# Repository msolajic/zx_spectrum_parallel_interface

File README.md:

# zx_spectrum_parallel_interface
Hardware design for a 3-port Parallel Interface for the Sinclair ZX Spectrum computer, with accompanying software examples.

This project is free to use and you can use any PCB manufacturer by downloading the Gerber files, but if you would like to support my work and help with further hardware development you can order these PCBs on PCBWay trough this link:

You will get cheap and professionally made PCBs, I will get credits that will help with this and [other projects](https://www.pcbway.com/project/member/?bmbno=1DE407A1-1650-47). Also, if you have to register to that site, [you can use this link](https://pcbway.com/g/YFnBAc) to get bonus initial credit.

Hardware Description
--------------------
The interface adds three 8-bit general-purpose buffered input-output ports to the ZX Spectrum, enabling you to create additional boards which use these ports as A/D or D/A convertres, motor drivers, relays, or, for example, use some Arduino modules. It also has an on-board Joystick port (on standard Port 31 for Kempston interface compatibility) and a Parallel (Centronics compatible) printer port.

It is built with Intel 8255 PPI chip, which is programmable - each 8-bit port can be set to either input or output (and there are special modes which split the 3rd port in 4 inputs and 4 outputs or enable handshaking). Refer to the [Intel 8255 documentation](./images/8255_intel.pdf "Intel 8255 documentation") for details.

The Interface is based on similar interfaces, especially [UR-4](https://cygnus.speccy.cz/popis_mhb8255.php "UR-4") and [UPI](https://cygnus.speccy.cz/popis_upi-jiiira-8255.php "UPI")

A 74LS688 forms an address decoder, to fully decode the addresses in the Input/Output Address space, so no "ghost" addresses can trigger the interface. 74LS04 is used to invert the RESET signal (as the 8255 requires a positive logic signal there) and to invert the STROBE signal for the printer. 74LS540 is used as an additional 3-state buffer for the Joystick port, which can be disabled via a switch (if you don't need the joystick port and plan to use the port A for other purposes)

Port Pinouts
------------

#### Joystick port

| DB-9 Pin | Port A | Joystick | Amiga Mouse       |
|:--------:|:------:|:--------:|:-----------------:|
| 1        | 3      | Up       | Y2 (YB)           |
| 2        | 2      | Down     | X1 (XA)           |
| 3        | 1      | Left     | Y1 (YA)           |
| 4        | 0      | Right    | X2 (XB)           |
| 5        | 6      |          | Button 3 (Middle) |
| 6        | 4      | Fire 1   | Button 1 (Left)   |
| 7        |        | +5V      | +5V               |
| 8        |        | GND      | GND               |
| 9        | 5      | Fire 2   | Button 2 (Right)  | 

When the joystick port is enabled, bit 7 of Port A is always 0.

#### Printer port

| DB-25 Pin | 8255 port   | Function   |
|:---------:|:-----------:|:----------:|
| 1         | C3 inverted | /STROBE    |
| 2         | B0          | Data bit 0 |
| 3         | B1          | Data bit 1 |
| 4         | B2          | Data bit 2 |
| 5         | B3          | Data bit 3 |
| 6         | B4          | Data bit 4 |
| 7         | B5          | Data bit 5 |
| 8         | B6          | Data bit 6 |
| 9         | B7          | Data bit 7 |
| 11        | C7          | BUSY       |
| 17        | Jumper JP1  | /SELECT    |
| 18-25     | GND         | GND        |

Some printers require pin 17 (/SELECT) pulled low. In case your printer doesn't work, short the jumper JP1.

#### 40-pin connector

| Pin | Function | | Function | Pin |
|:---:|:--------:|-|:--------:|:---:|
| 1   | A0       | | A1       | 2   |
| 3   | A2       | | A3       | 4   |
| 5   | A4       | | A5       | 6   |
| 7   | A6       | | A7       | 8   |
| 9   | GND      | | GND      | 10  |
| 11  | GND      | | GND      | 12  |
| 13  | C0       | | C1       | 14  |
| 15  | C2       | | C3       | 16  |
| 17  | C4       | | C5       | 18  |
| 19  | C6       | | C7       | 20  |
| 21  | GND      | | GND      | 22  |
| 23  | GND      | | GND      | 24  |
| 25  | B0       | | B1       | 26  |
| 27  | B2       | | B3       | 28  |
| 29  | B4       | | B5       | 30  |
| 31  | B6       | | B7       | 32  |
| 33  | NC       | | NC       | 34  |
| 35  | +9V      | | +9V      | 36  |
| 37  | NC       | | NC       | 38  |
| 39  | +5V      | | +5V      | 40  |

The connector is wired directly to the 8255 ports. +5v and +9v are from the ZX Spectrum regulator and power supply respectively. As the +5v regulator in an 48k ZX Spectrum is already at its limits, this power supply can be used only for simple logic, not for driving motors etc. For +9v output, I recommend using maximum 200mA.

Usage
-----

The interface uses the following addresses:

| Port         | Binary   | Decimal | Hex  |
|:------------:|:--------:|:-------:|:----:|
| Port A       | 00011111 | 31      | 0x1f |
| Port B       | 00111111 | 63      | 0x3f |
| Port C       | 01011111 | 95      | 0x5f |
| Control Word | 01111111 | 127     | 0x7f |

After a RESET, all ports are set as inputs. This enables the use of the Joystick port without any initialization. Setting up the direction of the ports is simple, writing a byte to the Control Word register. In Mode 0 (the simplest mode of operation for the 8255) the configuration bytes are as follows:

| Binary   | Decimal | Functions                         |
|:--------:|:-------:|:---------------------------------:|
| 10000000 | 128     | A = out B = out CL = out CH = out |
| 10000001 | 129     | A = out B = out CL = in  CH = out |
| 10000010 | 130     | A = out B = in  CL = out CH = out |
| 10000011 | 131     | A = out B = in  CL = in  CH = out |
| 10001000 | 136     | A = out B = out CL = out CH = in  |
| 10001001 | 137     | A = out B = out CL = in  CH = in  |
| 10001010 | 138     | A = out B = in  CL = out CH = in  |
| 10001011 | 139     | A = out B = in  CL = in  CH = in  |
| 10010000 | 144     | A = in  B = out CL = out CH = out |
| 10010001 | 145     | A = in  B = out CL = in  CH = out |
| 10010010 | 146     | A = in  B = in  CL = out CH = out |
| 10010011 | 147     | A = in  B = in  CL = in  CH = out |
| 10011000 | 152     | A = in  B = out CL = out CH = in  |
| 10011001 | 153     | A = in  B = out CL = in  CH = in  |
| 10011010 | 154     | A = in  B = in  CL = out CH = in  |
| 10011011 | 155     | A = in  B = in  CL = in  CH = in  |

Mode 1 enables handshaking (with port C being used for handshaking signaling), and Mode 2 enables bidirectional data transfer on port A, port B is disabled, and port C is used for handshaking. This is covered in more depth in the 8255 datasheet.

#### Printing from BASIC

A very simple BASIC program can be used to print some text. This program will probably only work on Dot-Matrix printers. Inkjet and Laser printers usually don't understand raw text, they require graphics data to be sent either via ESC/P or PCL commands.

    10 GO SUB 9000: REM INITIALIZE
    20 LET A$="This is the text to be printed"
    30 GO SUB 9100: REM LPRINT A$
    40 GO SUB 9200: REM CR+LF
    50 GO SUB 9300: REM FF
    60 STOP
    9000 REM INITIALIZE
    9010 OUT 127,152
    9020 RETURN
    9100 REM LPRINT A$
    9110 FOR N=1 TO LEN (A$)
    9120 LET CHAR=CODE(A$(N))
    9130 OUT 63,CHAR
    9140 OUT 95,255: REM /STROBE 0
    9150 OUT 95,0: REM /STROBE 1
    9160 NEXT N
    9170 RETURN
    9200 REM CR+LF
    9210 OUT 63,13
    9220 OUT 95,255: REM /STROBE 0
    9230 OUT 95,0: REM /STROBE 1
    9240 OUT 63,10
    9250 OUT 95,255: REM /STROBE 0
    9260 OUT 95,0: REM /STROBE 1
    9270 RETURN
    9300 REM FF
    9310 OUT 63,12
    9320 OUT 95,255: REM /STROBE 0
    9330 OUT 95,0: REM /STROBE 1
    9340 RETURN
    
You can find this program in the examples folder, in .bas, .tap and .wav format. Note that the BUSY line is not taken into account in this example. It is actually not needed, as the BASIC is very slow in contrast to Assembler. 

It is better to use Assembler routines as they will allow for using LPRINT and LLIST commands from BASIC. In the examples folder, I have provided a simple printer driver which resides in the (ZX Printer) printer buffer. Alongside text printing, it provides a routine to copy the graphical content of the screen to the printer. Note that the semigraphics characters and UDGs will not be printed (or will be printed with their ASCII code equivalent).

Another assembly routine provided is one that prints the screen in 3x the size, with shading. This was printed in the magazine [Your Spectrum, Issue 4, June 1984](http://www.users.globalnet.co.uk/~jg27paw4/yr04/yr04_55.htm), by Andrew Pennell. I have adapted it to use this interface.

I have used [PASMO](https://pasmo.speccy.org/ "PASMO") to assemble the sources, but you can use any other Z80 assembler. BASIC files were converted to .tap wit [bas2tap](https://github.com/speccyorg/bas2tap "bas2tap"). Tape to WAV conversion was done with [zxtap-to-wav](https://github.com/raydac/zxtap-to-wav "zxtap-to-wav")

Revision history
----------------

- Rev.1
    - Initial release

License
-------
zx_spectrum_parallel_interface is Open Hardware licensed under the [CERN OHL P v2](https://ohwr.org/cern_ohl_p_v2.txt), released by Marko Šolajić in 2025. You may redistribute and modify this documentation under the terms of the CERN OHL P v2.

A copy of the full license is included in file [license.txt](license.txt)

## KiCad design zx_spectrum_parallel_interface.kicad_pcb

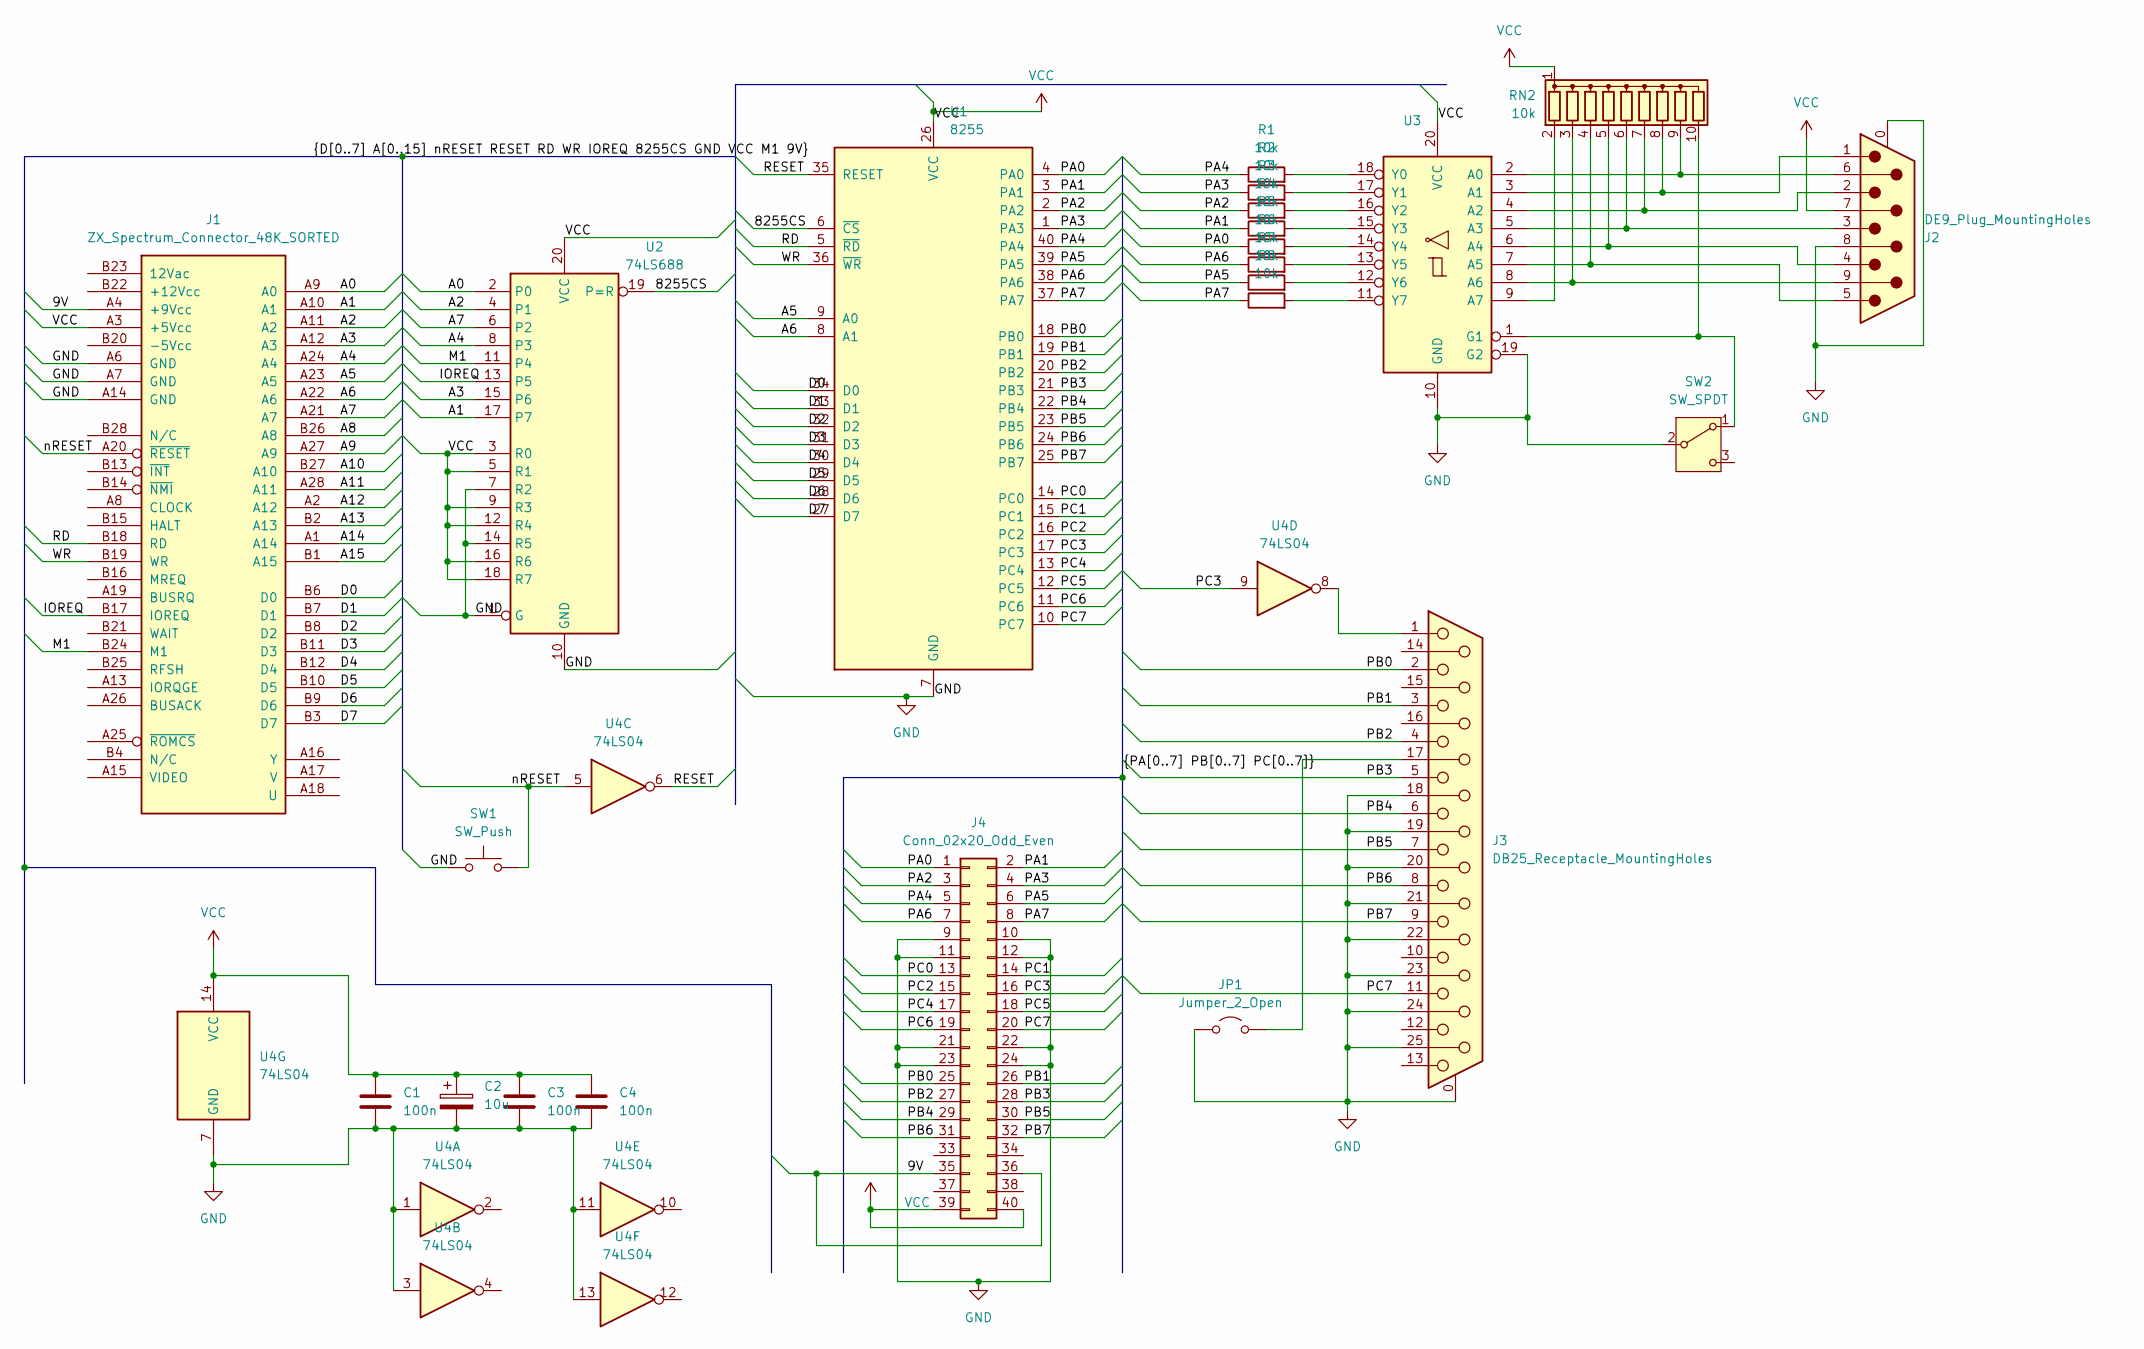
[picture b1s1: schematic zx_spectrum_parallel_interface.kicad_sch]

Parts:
C1, C3, C4: 100n; C_0805_2012Metric_Pad1.18x1.45mm_HandSolder
C2: 10u; CP_Radial_D4.0mm_P2.00mm
J1: ZX_Spectrum_Connector_48K_SORTED; ZX_CONN
J2: DE9_Plug_MountingHoles; DSUB-9_Male_Horizontal_P2.77x2.84mm_EdgePinOffset4.94mm_Hou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
J3: DB25_Receptacle_MountingHoles; DSUB-25_Female_Horizontal_P2.77x2.84mm_EdgePinOffset4.94mm_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
J4: Conn_02x20_Odd_Even; IDC-Header_2x20_P2.54mm_Vertical
JP1: Jumper_2_Open; TestPoint_2Pads_Pitch2.54mm_Drill0.8mm
R1, R2, R3, R4, R5, R6, R7, R8: 10k; R_0805_2012Metric_Pad1.20x1.40mm_HandSolder
RN2: 10k; R_Array_SIP10
SW1: SW_Push; SW_PUSH_6mm
SW2: SW_SPDT; SW_Slide_1P2T_3mm
U1: 8255; DIP-40_W15.24mm
U2: 74LS688; DIP-20_W7.62mm
U3: 74LS540; DIP-20_W7.62mm
U4: 74LS04

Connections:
/9V: J1.A4 (+9Vcc), J4.35, J4.36
/8255CS: U1.6 (~CS), U2.19 (P=R)
/A0: J1.A9 (A0), U2.2 (P0)
/A1: J1.A10 (A1), U2.17 (P7)
/A2: J1.A11 (A2), U2.4 (P1)
/A3: J1.A12 (A3), U2.15 (P6)
/A4: J1.A24 (A4), U2.8 (P3)
/A5: J1.A23 (A5), U1.9 (A0)
/A6: J1.A22 (A6), U1.8 (A1)
/A7: J1.A21 (A7), U2.6 (P2)
/A8: J1.B26 (A8)
/A9: J1.A27 (A9)
/A10: J1.B27 (A10)
/A11: J1.A28 (A11)
/A12: J1.A2 (A12)
/A13: J1.B2 (A13)
/A14: J1.A1 (A14)
/A15: J1.B1 (A15)
/D0: J1.B6 (D0), U1.34 (D0)
/D1: J1.B7 (D1), U1.33 (D1)
/D2: J1.B8 (D2), U1.32 (D2)
/D3: J1.B11 (D3), U1.31 (D3)
/D4: J1.B12 (D4), U1.30 (D4)
/D5: J1.B10 (D5), U1.29 (D5)
/D6: J1.B9 (D6), U1.28 (D6)
/D7: J1.B3 (D7), U1.27 (D7)
/IOREQ: J1.B17 (IOREQ), U2.13 (P5)
/M1: J1.B24 (M1), U2.11 (P4)
/PA0: J4.1, R5.1, U1.4 (PA0)
/PA1: J4.2, R4.1, U1.3 (PA1)
/PA2: J4.3, R3.1, U1.2 (PA2)
/PA3: J4.4, R2.1, U1.1 (PA3)
/PA4: J4.5, R1.1, U1.40 (PA4)
/PA5: J4.6, R7.1, U1.39 (PA5)
/PA6: J4.7, R6.1, U1.38 (PA6)
/PA7: J4.8, R8.1, U1.37 (PA7)
/PB0: J3.2, J4.25, U1.18 (PB0)
/PB1: J3.3, J4.26, U1.19 (PB1)
/PB2: J3.4, J4.27, U1.20 (PB2)
/PB3: J3.5, J4.28, U1.21 (PB3)
/PB4: J3.6, J4.29, U1.22 (PB4)
/PB5: J3.7, J4.30, U1.23 (PB5)
/PB6: J3.8, J4.31, U1.24 (PB6)
/PB7: J3.9, J4.32, U1.25 (PB7)
/PC0: J4.13, U1.14 (PC0)
/PC1: J4.14, U1.15 (PC1)
/PC2: J4.15, U1.16 (PC2)
/PC3: J4.16, U1.17 (PC3), U4.9
/PC4: J4.17, U1.13 (PC4)
/PC5: J4.18, U1.12 (PC5)
/PC6: J4.19, U1.11 (PC6)
/PC7: J3.11, J4.20, U1.10 (PC7)
/RD: J1.B18 (RD), U1.5 (~RD)
/RESET: U1.35 (RESET), U4.6
/WR: J1.B19 (WR), U1.36 (~WR)
/nRESET: J1.A20 (~RESET), SW1.2, U4.5
GND: C1.2, C2.2, C3.2, C4.2, J1.A6 (GND), J1.A7 (GND), J1.A14 (GND), J2.0 (PAD), J2.8, J3.0 (PAD), J3.18, J3.19, J3.20, J3.21, J3.22, J3.23, J3.24, J3.25, J4.9, J4.10, J4.11, J4.12, J4.21, J4.22, J4.23, J4.24, JP1.1 (A), SW1.1, SW2.2 (B), U1.7 (GND), U2.1 (G), U2.7 (R2), U2.10 (GND), U2.14 (R5), U3.10 (GND), U3.19 (G2), U4.1, U4.3, U4.7 (GND), U4.11, U4.13
unnamed: J3.17, JP1.2 (B)
unnamed: J3.1, U4.8
unnamed: RN2.2 (R1), U3.9 (A7)
unnamed: J2.9, RN2.3 (R2), U3.8 (A6)
unnamed: J2.5, RN2.4 (R3), U3.7 (A5)
unnamed: J2.4, RN2.5 (R4), U3.6 (A4)
unnamed: J2.3, RN2.6 (R5), U3.5 (A3)
unnamed: J2.2, RN2.7 (R6), U3.4 (A2)
unnamed: J2.1, RN2.8 (R7), U3.3 (A1)
unnamed: J2.6, RN2.9 (R8), U3.2 (A0)
unnamed: RN2.10 (R9), SW2.1 (A), U3.1 (G1)
unnamed: R1.2, U3.18 (Y0)
unnamed: R2.2, U3.17 (Y1)
unnamed: R3.2, U3.16 (Y2)
unnamed: R4.2, U3.15 (Y3)
unnamed: R5.2, U3.14 (Y4)
unnamed: R6.2, U3.13 (Y5)
unnamed: R7.2, U3.12 (Y6)
unnamed: R8.2, U3.11 (Y7)
VCC: C1.1, C2.1, C3.1, C4.1, J1.A3 (+5Vcc), J2.7, J4.39, J4.40, RN2.1 (common), U1.26 (VCC), U2.3 (R0), U2.5 (R1), U2.9 (R3), U2.12 (R4), U2.16 (R6), U2.18 (R7), U2.20 (VCC), U3.20 (VCC), U4.14 (VCC)

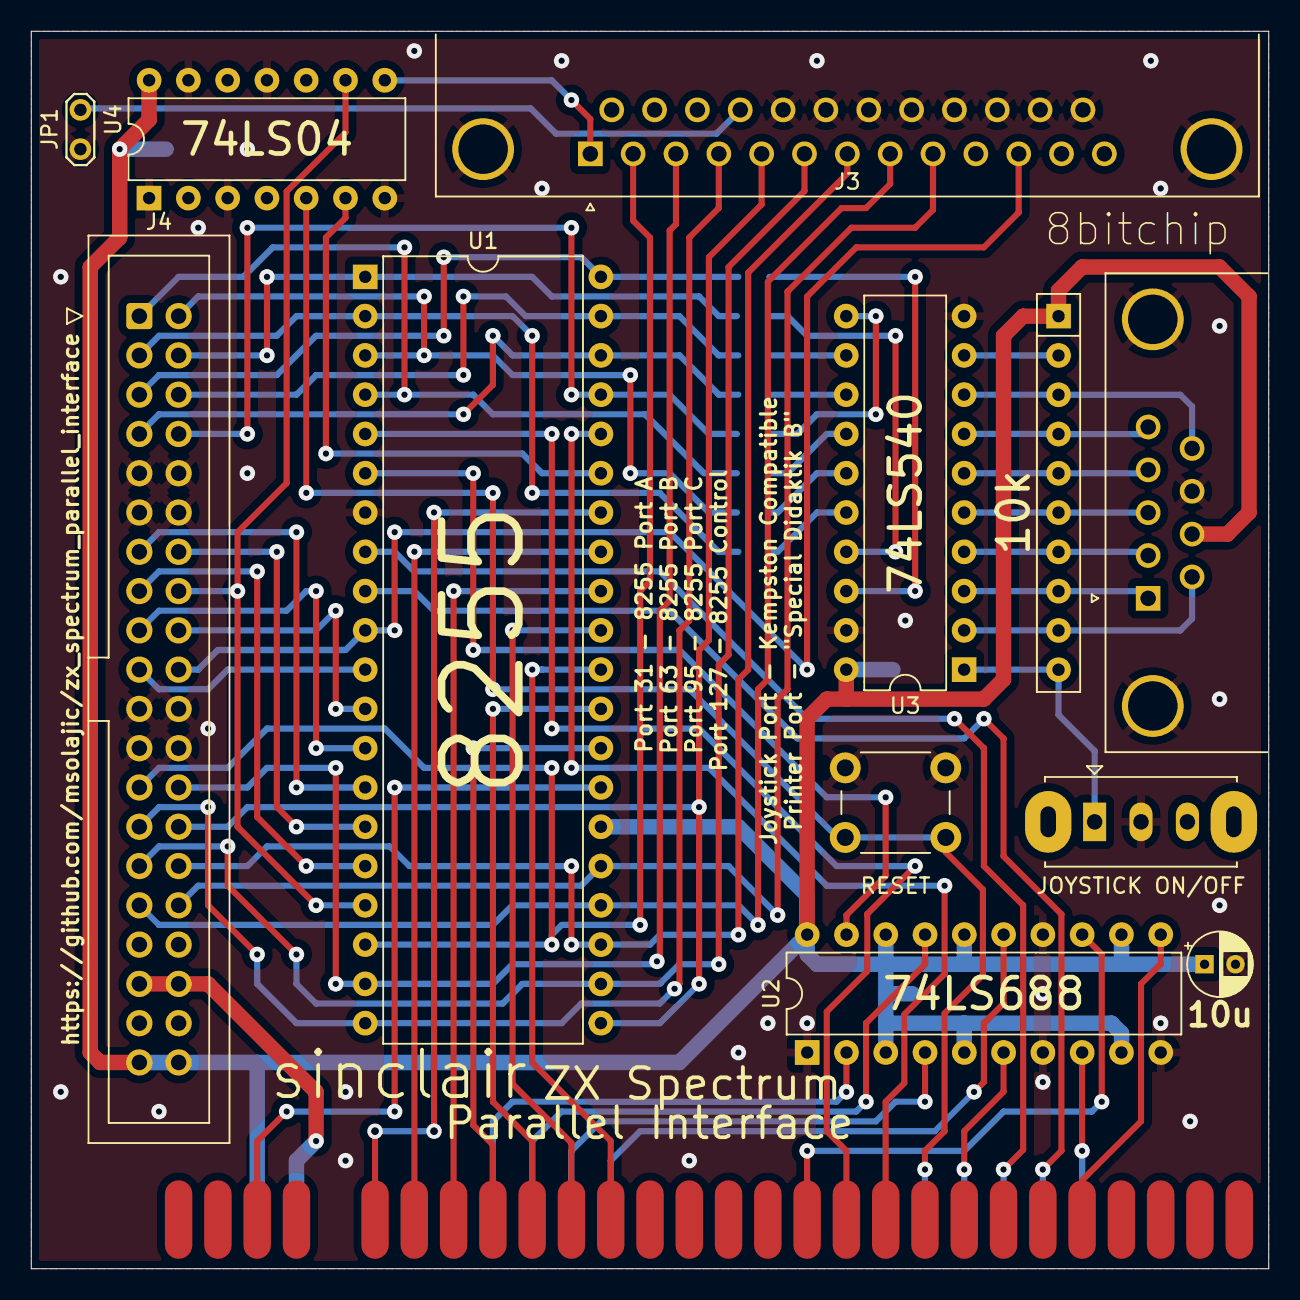
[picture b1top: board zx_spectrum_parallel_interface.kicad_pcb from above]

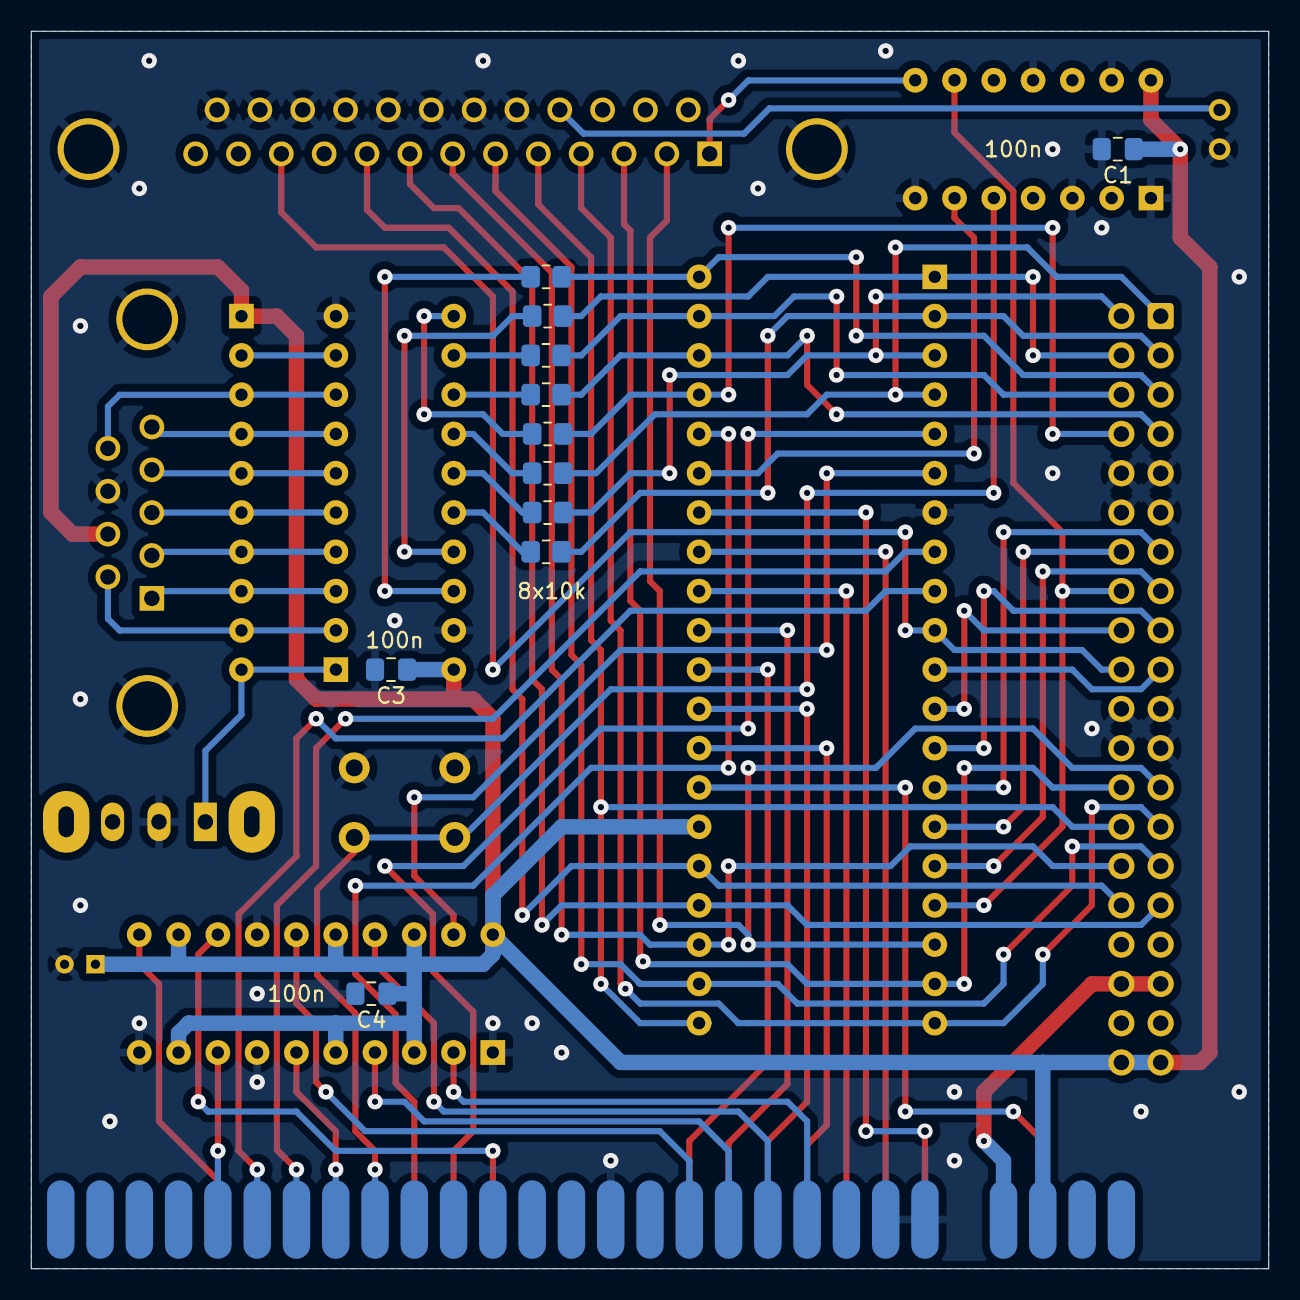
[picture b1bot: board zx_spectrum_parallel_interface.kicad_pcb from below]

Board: 2 copper layers, 80.0 x 80.0 mm, 24 parts (11 on the bottom side), 69 nets.

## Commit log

2025-02-12 Initial upload
